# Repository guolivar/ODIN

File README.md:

ODIN
====
Outdoor Dust Information Node (ODIN)

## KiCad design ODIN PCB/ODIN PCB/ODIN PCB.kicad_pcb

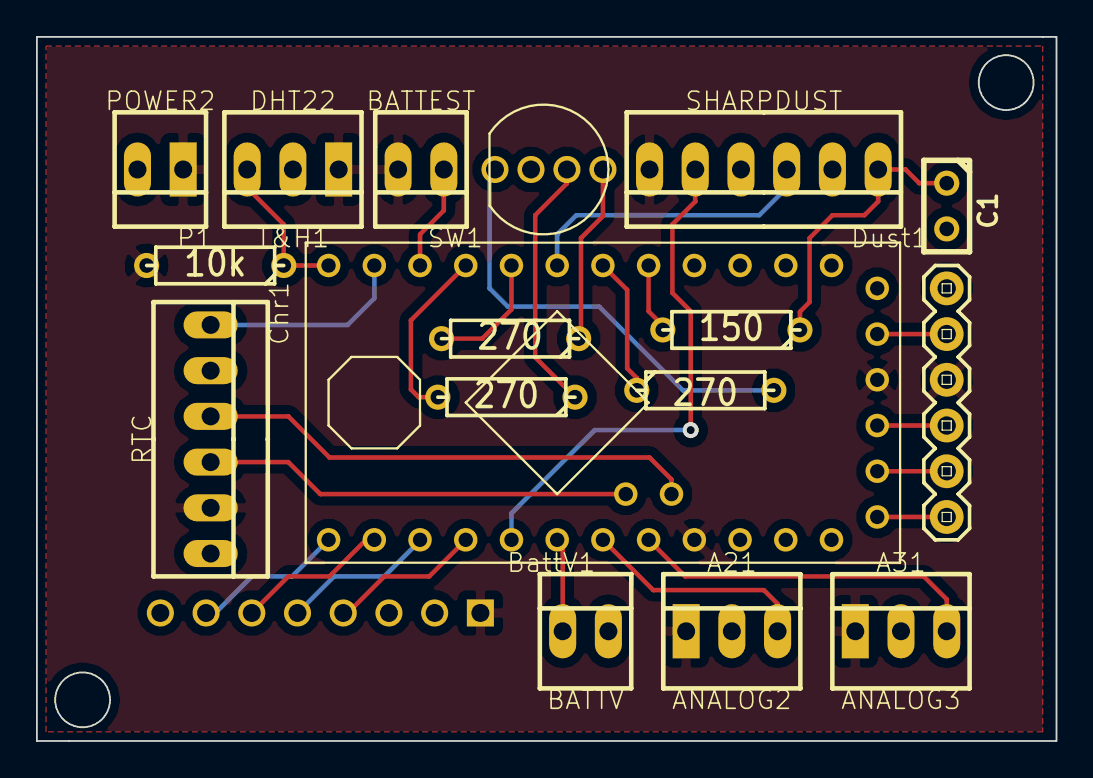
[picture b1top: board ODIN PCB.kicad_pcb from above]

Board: 2 copper layers, 56.6 x 39.1 mm, 18 parts (1 on the bottom side), 28 nets.

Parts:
A21: ANALOG2; header3
A31: ANALOG3; header3
APM1: ARDUINO_PROMINI; Halley-ARDUINO_PRO_MINI
BattV1: BATTV; PINHEAD1-2
C1: 220u; C1
Chr1: RTC; PINHEAD1-6
Dust1: SHARPDUST; PINHEAD1-6
GUS1: RGBLED; SparkFun-LED-TRICOLOR-THROUGHHOLE
JP1: FTDI_BASICPTH; SparkFun-FTDI_BASIC
P1: POWER2; conn2pwr
R1: 10k; R3
R2, R3, R4: 270; R3
R5: 150; R3
SD1: MICRO-SD; microSD
SW1: BATTEST; PINHEAD1-2
T&H1: DHT22; header3

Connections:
/A0: APM1.A0, Dust1.5
/A1: APM1.A1, BattV1.1
/A2: A21.3, APM1.A2
/A3: A31.3, APM1.A3
/CLK: APM1.D13, SD1.5
/CS: APM1.D10, SD1.2
/CTS: APM1.CTS, JP1.CTS
/D0: APM1.TXO, JP1.RXI
/D1: APM1.RXI, JP1.TXO
/D2: APM1.D2, R5.2
/D3: APM1.D3, R2.1
/D4: APM1.D4, Dust1.3
/D5: APM1.D5, R3.2
/D6: APM1.D6, R4.2
/D7: APM1.D7, SW1.1
/D9: APM1.D9, R1.1, T&H1.3
/DI: APM1.D11, SD1.3
/DO: APM1.D12, SD1.4
/DTR: APM1.GRN, JP1.DTR
/GND: A21.GND, A31.GND, APM1.GND1, BattV1.2, C1.2, Chr1.6, Dust1.2, Dust1.4, GUS1.GND, JP1.GND, P1.GND, SD1.6, T&H1.GND
/SCL: APM1.A4, Chr1.4
/SDA: APM1.A5, Chr1.3
/SQW: APM1.D8, Chr1.1
/VCC: A21.VCC, A31.VCC, APM1.VCC1, APM1.VCC2, Chr1.5, Dust1.6, JP1.VCC, P1.VCC, R1.2, SD1.8, SW1.2, T&H1.VCC
unnamed: GUS1.RED, R2.2
unnamed: GUS1.GRN, R3.1
unnamed: GUS1.BLU, R4.1
unnamed: C1.1, Dust1.1, R5.1

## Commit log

2014-07-07 Firmware for ODIN. v1
2014-07-07 First push that makes sense.
2014-07-09 PCB design first commit. Working schematic with no traces on the PCB.
2014-07-14 Next iteration. Better net labelling. From Sam's message: "I've got it down to about 40mm x 56 mm. Probably needs checking for connectivity issues and errors. It passed the KiCad design rules check. 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
2014-08-21 Dust trigger pin changed to 4 on new ODIN PCB
2014-08-21 Interrupt pinmode set to INPUT_PULLUP
2014-08-28 Swapped SDA/SCL pins, moved RTC alarm trigger to Arduino pin 2 interrupt. RGB led leg on pin 2 moved to pin 8. Libraries added as some parts within libraries modified.
2014-08-28 ODIN sleeps until interrupt on pin 2 is triggered. RTC alarm provides interrupt. RTC no longer connected to pin 8.
2014-08-29 Added arduino sleep. Alarm from RTC used as interrupt on pin 2 to wake arduino. RTC alarm no longer connected to pin 8.
2015-05-15 GIT told me to do it
2015-05-15 Changed tree to make it easier to work with Kicad
2015-09-03 20 1s dust samples per minute and an indication of memory card status on LED (pin 13)
2015-09-07 Potential error on Arduino 1.0.6 declaring counters in the for cycle definition. Memory card initialisation status light fixed.
2015-10-08 Fixed bug where ODIN would fail to wake up because of bad timing in the start sequence
2015-10-08 Dirty merge
2016-02-02 Updated firmware for U de Chile's implementation of ODIN.
2016-02-02 Cleaned the firmware removing redundant and outdated libraries.
2016-02-16 Corrected compiling errors
    Fixed non-inclusion of SD library
    Fixed wrong call to read temperature/RH
    Fixed missing ;
    Tested compiling with Arduino 1.6.4
2016-04-07 Libraries updated
2016-04-08 Added gus library from odin-sd
